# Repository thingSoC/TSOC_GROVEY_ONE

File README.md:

# TSOC_GROVEY_ONE
**TSOC_GROVEY_ONE** is a ATMEGA328 based board, an Embedded Module for thingSoC compatible with the Arduino IDE.

The **TSOC_GROVEY_ONE** allows you to connect [thingSoC](http://thingsoc.github.io/), [Mikrobus](http://www.mikroe.com/mikrobus/), 
and/or [Grove System](http://www.seeedstudio.com/blog/2016/03/09/tutorial-intro-to-grove-connectors-for-arduinoraspberry-pi-projects/) 
Modules all at the same time, using the Arduino Development environment, with the the ATMEGA328P processor.
This gives you maximum flexiblity for sensor and actuator, selection and reuse. 

The thingSoC "Grovey Series" was designed as "Everyday Electronics", a no-frills, low cost, approach to modular embedded product design.
thingSoC boards are similar in size to most break-out-boards (BOBs), but feature a standardized stacking pinout, as well as an I2C metadata store (EEPROM)
to indicate what peripherals are installed.

---------------------------------------

[TSOC_GROVEY_ONE](https://github.com/thingSoC/TSOC_GROVEY_ONE/)

* [thingSoC Compliant Module](http://www.thingsoc.com)
* [Mikrobus Compatible Module](http://www.mikroe.com/mikrobus/) 
* 5V Nominal Power Input
* 5V or 3.3V Operation
* Supports Analog  Inputs  (ADC) 
* Supports Digital Outputs (GPIO)
* Supports Digital Inputs  (GPIO)
* Supports I2C Interface
* Supports UART Interface
* Supports SPI Interface

---------------------------------------
## Example Applications

* [Weather Sensor](http://www.mikroe.com/click/weather/) BOSCH BME280 Temp, Humidity, Air Pressure
* [Methane Sensor](http://www.mikroe.com/click/methane/) MQ-4 Sensor for Methane (CH4) 
* [Air Quality Sensor](http://www.mikroe.com/click/air-quality/) MQ-135 Sensor for Harmful Gasses
* [Lightning Sensor](http://www.mikroe.com/click/thunder/) AS3935 Lighting Strike Detector
* [Controlled Relay](http://www.mikroe.com/click/relay/) G6D1AASI Power Relay Control Module

---------------------------------------
## 3D Model (Sketchup)

---------------------------------------
## Project Status

* 09/02/2016 : Revision 2.0 Release for PCB fab

## Revision 2.0 Notes: ##

* Add FTDI Connector

---------------------------------------

## Documentation Index <a name="documentation_index"/>

[Quick Start Guide](https://github.com/thingSoC/TSOC_GROVEY_ONE/blob/master/TSOC_GROVEY_ONE/docs/QuickStart.md)

[User Guide](https://github.com/thingSoC/TSOC_GROVEY_ONE/blob/master/TSOC_GROVEY_ONE/docs/UserGuide.md)

[Theory of Operation](https://github.com/thingSoC/TSOC_GROVEY_ONE/blob/master/TSOC_GROVEY_ONE/docs/TheoryOfOperation.md)

[thingSoC Organization Website](http://thingSoC.github.io)

[thingSoC FAQ - Frequently Asked Questions](http://thingsoc.github.io/support/faq.html)

---------------------------------------

[  
*thingSoC*](http://thingsoc.github.io)

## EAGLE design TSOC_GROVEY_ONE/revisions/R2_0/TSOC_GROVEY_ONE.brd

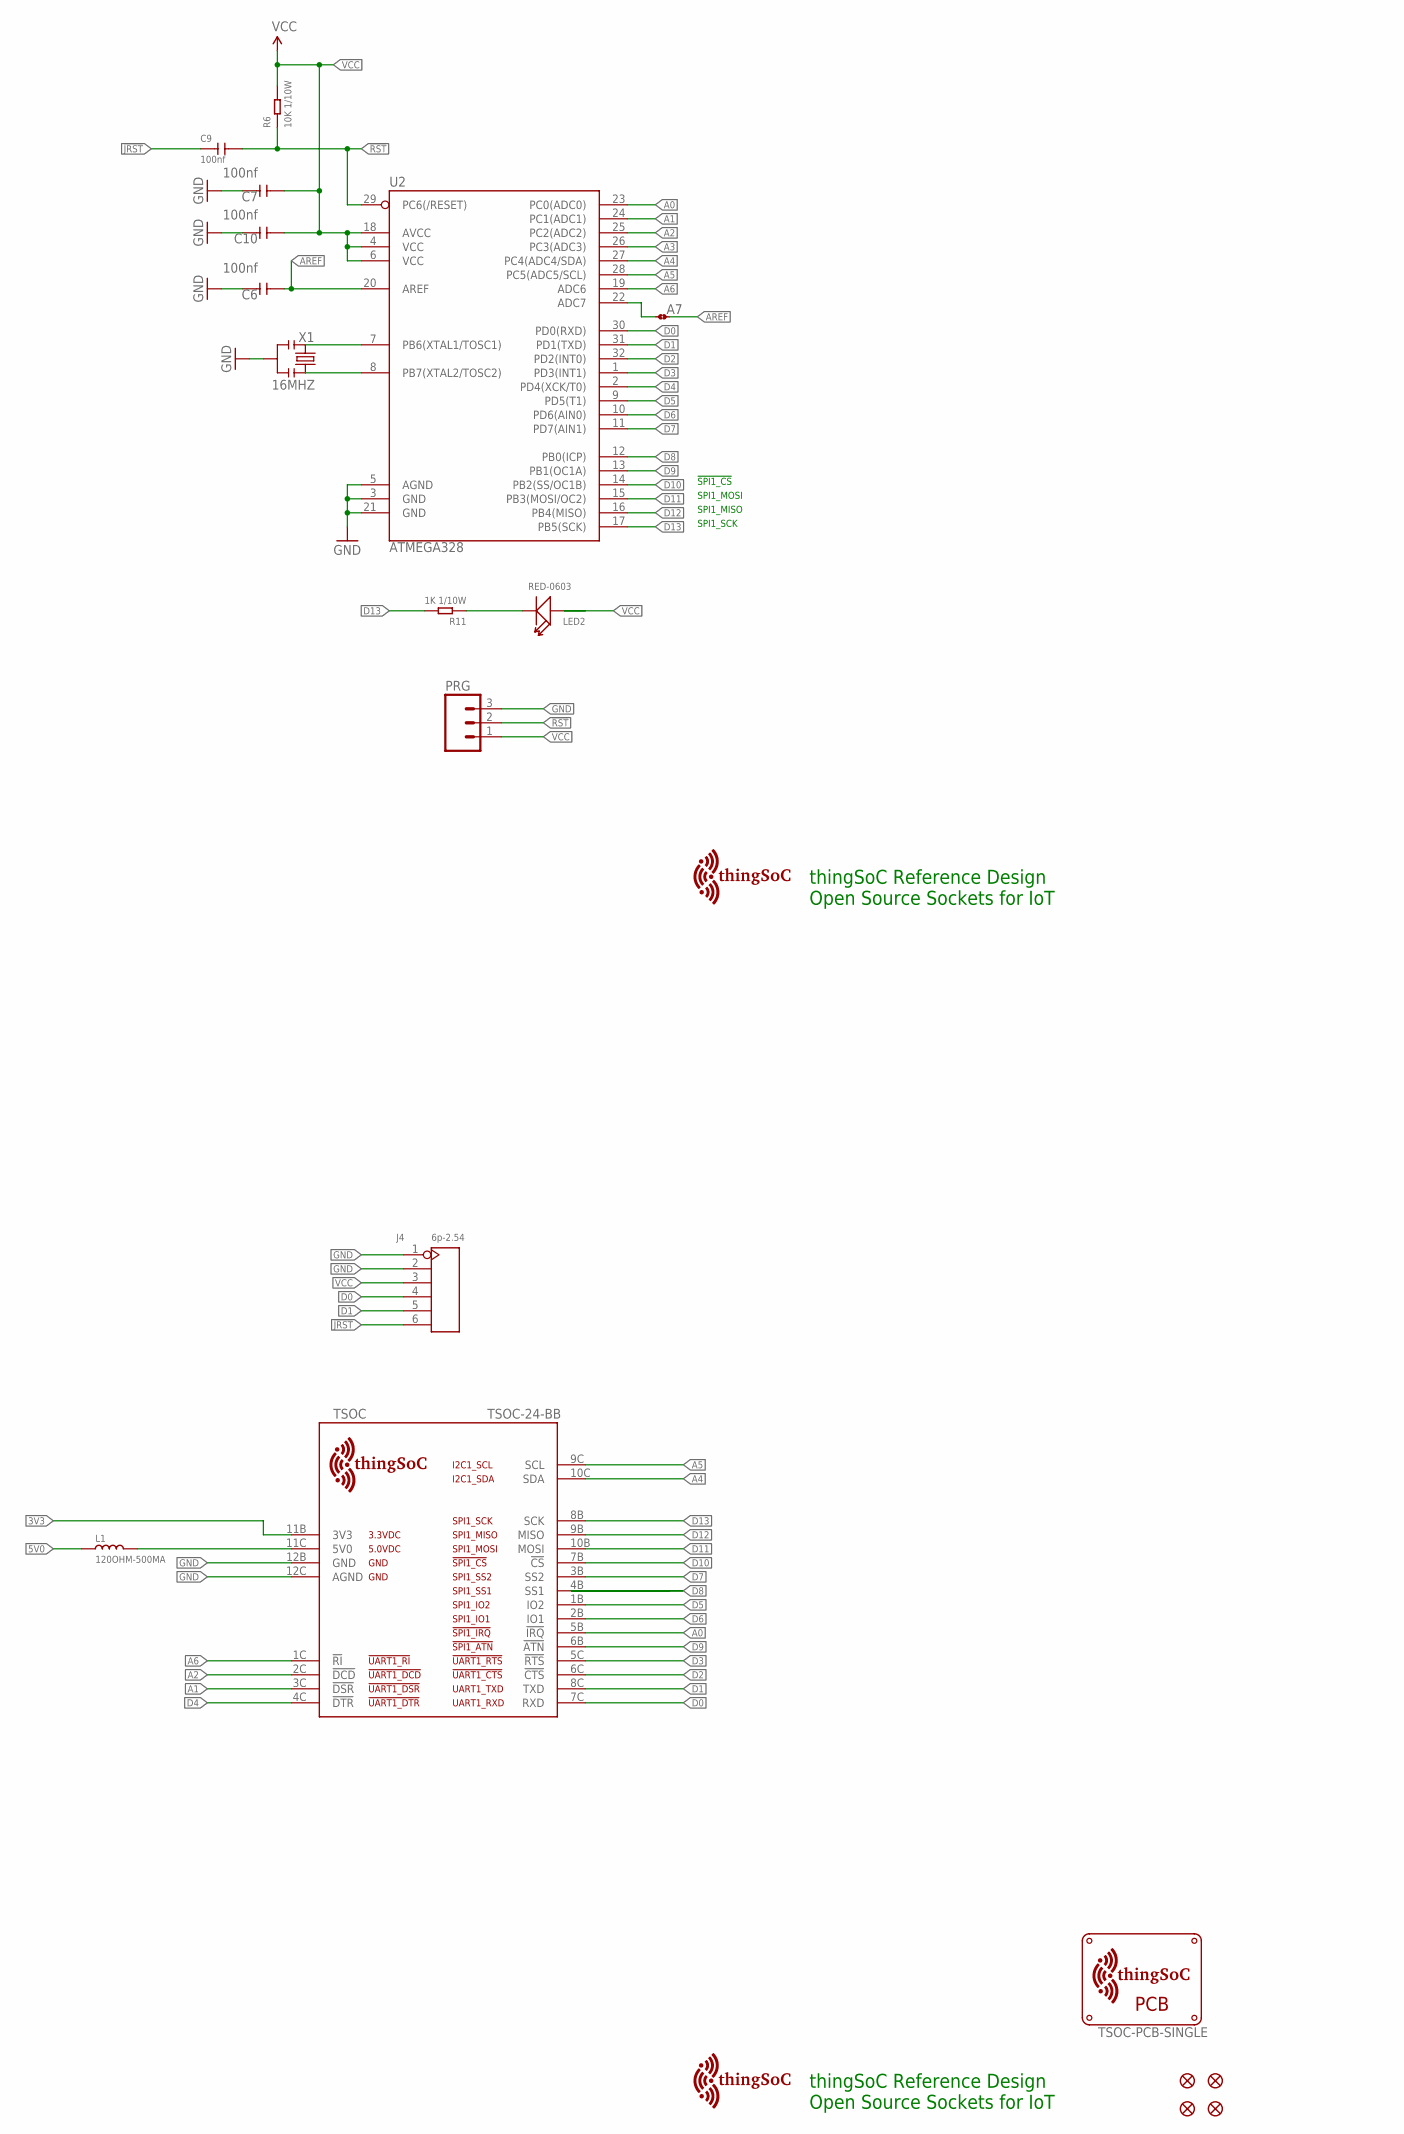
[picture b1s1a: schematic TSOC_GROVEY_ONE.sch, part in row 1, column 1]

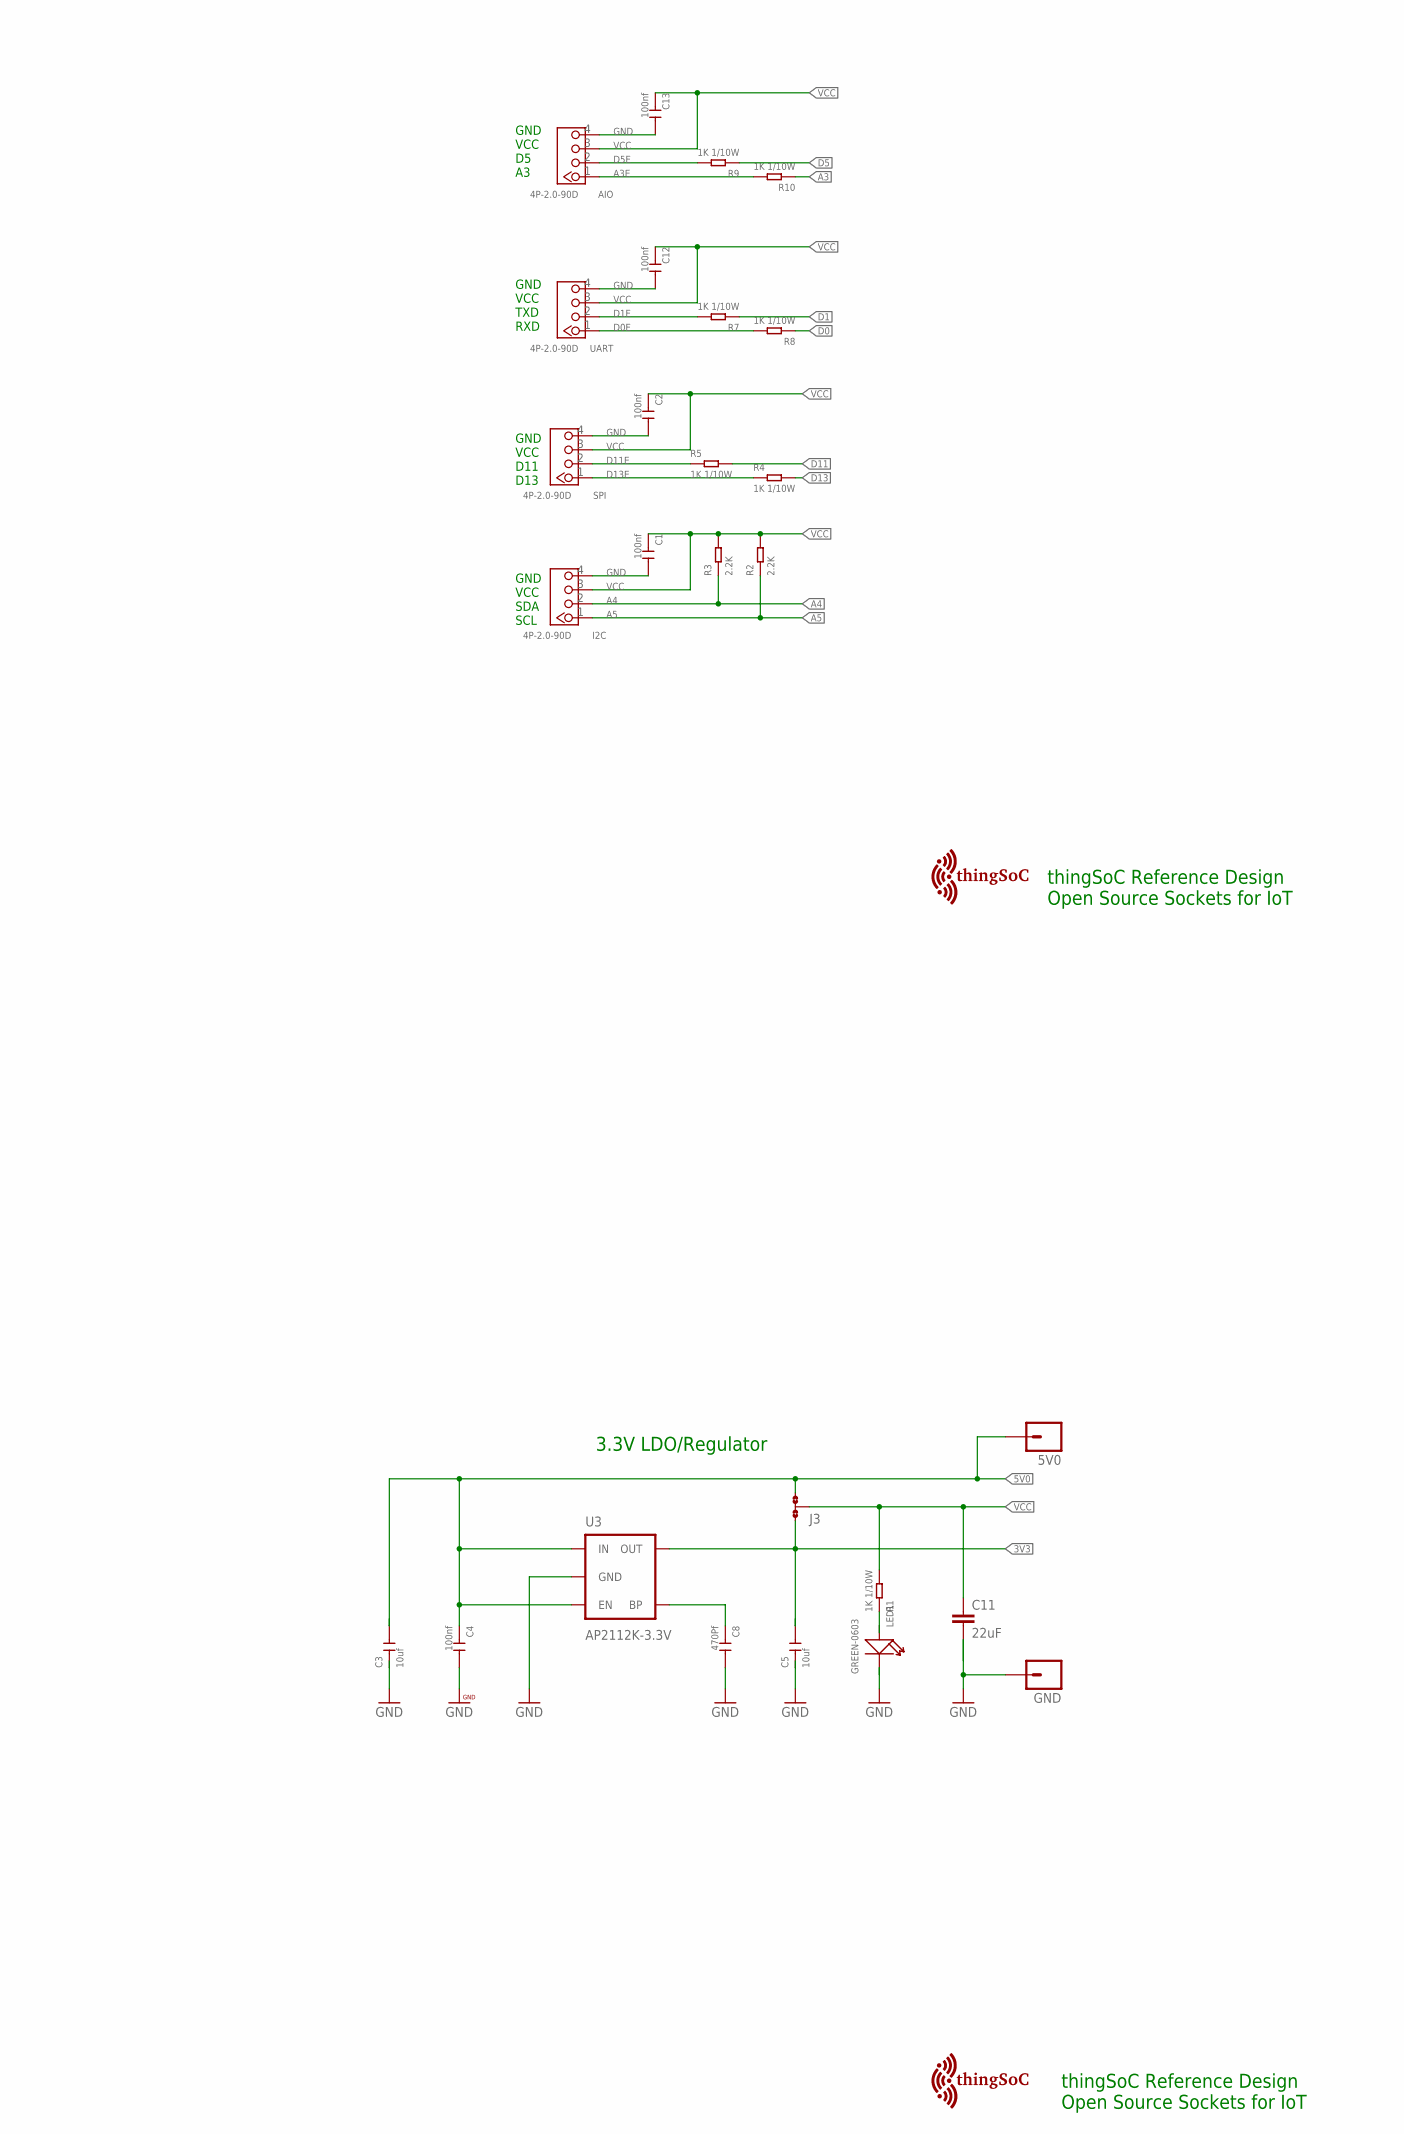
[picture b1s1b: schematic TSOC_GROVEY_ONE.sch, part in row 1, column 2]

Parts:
5V0: M01PTH; 1X01
$$U$1: TSOC-PCB-SINGLE; TSOC-BB-BRD-DIM
A7: JMP-2-NO
AIO: 4P-2.0-90D; HW4-2.0-90D
C1, C2, C4, C6, C7, C9, C10, C12, C13: 100nf; C0603
C3, C5: 10uf; C0603
C8: 470Pf; C0603
C11: 22uF; EIA-1206
FID1, FID2, FID3, FID4: FIDUCIALUFIDUCIAL; MICRO-FIDUCIAL
GND: M01PTH; 1X01
I2C: 4P-2.0-90D; HW4-2.0-90D
J3: NO; JMP-3-NO-PTH-2.54
J4: 6p-2.54; H6-2.54
L1: 120OHM-500MA; L0603
LED1: GREEN-0603; LED-0603
LED2: RED-0603; LED-0603
PRG: M03PTH; 1X03
R1, R4, R5, R7, R8, R9, R10, R11: 1K 1/10W; R0603
R2, R3: 2.2K; R0603
R6: 10K 1/10W; R0603
SPI: 4P-2.0-90D; HW4-2.0-90D
TSOC: TSOC-24-BB; TSOC-BB-S24
U2: ATMEGA328; TQFP32-08
U3: AP2112K-3.3V; SOT23-5
U$1, U$101, U$103: TSOC-LOGO-SMALL; TSOC-LOGO-SML
U$102: TSOC-LOGO-LRG
UART: 4P-2.0-90D; HW4-2.0-90D
X1: 16MHZ; X3-SMD-3.6X1.3X0.8MM

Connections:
3V3: C5.2, J3.1, TSOC.11B (3V3), U3.5 (OUT)
5V0: 5V0.1, C3.2, C4.1, J3.3, L1.1, U3.1 (IN), U3.3 (EN)
!JRST: C9.1, J4.6
!RST: C9.2, PRG.2, R6.1, U2.29 (PC6(/RESET))
A0: TSOC.5B (!IRQ), U2.23 (PC0(ADC0))
A1: TSOC.3C (!DSR), U2.24 (PC1(ADC1))
A2: TSOC.2C (!DCD), U2.25 (PC2(ADC2))
A3: R10.1, U2.26 (PC3(ADC3))
A3E: AIO.1, R10.2
A4: I2C.2, R3.1, TSOC.10C (SDA), U2.27 (PC4(ADC4/SDA))
A5: I2C.1, R2.1, TSOC.9C (SCL), U2.28 (PC5(ADC5/SCL))
A6: TSOC.1C (!RI), U2.19 (ADC6)
A7: A7.1, U2.22 (ADC7)
AREF: A7.2, C6.2, U2.20 (AREF)
BYPASS1: C8.1, U3.4 (BP)
D0: J4.4, R8.1, TSOC.7C (RXD), U2.30 (PD0(RXD))
D0E: R8.2, UART.1
D1: J4.5, R7.1, TSOC.8C (TXD), U2.31 (PD1(TXD))
D1E: R7.2, UART.2
D2: TSOC.6C (!CTS), U2.32 (PD2(INT0))
D3: TSOC.5C (!RTS), U2.1 (PD3(INT1))
D4: TSOC.4C (!DTR), U2.2 (PD4(XCK/T0))
D5: R9.1, TSOC.1B (IO2), U2.9 (PD5(T1))
D5E: AIO.2, R9.2
D6: TSOC.2B (IO1), U2.10 (PD6(AIN0))
D7: TSOC.3B (SS2), U2.11 (PD7(AIN1))
D8: TSOC.4B (SS1), U2.12 (PB0(ICP))
D9: TSOC.6B (!ATN), U2.13 (PB1(OC1A))
D10: TSOC.7B (!CS), U2.14 (PB2(SS/OC1B))
D11: R5.2, TSOC.10B (MOSI), U2.15 (PB3(MOSI/OC2))
D11E: R5.1, SPI.2
D12: TSOC.9B (MISO), U2.16 (PB4(MISO))
D13: R4.2, R11.2, TSOC.8B (SCK), U2.17 (PB5(SCK))
D13E: R4.1, SPI.1
GND: AIO.4, C1.2, C2.2, C3.1, C4.2, C5.1, C6.1, C7.1, C8.2, C10.1, C11.2, C12.2, C13.2, GND.1, I2C.4, J4.1, J4.2, LED1.-, PRG.3, SPI.4, TSOC.12B (GND), TSOC.12C (AGND), U2.3 (GND), U2.5 (AGND), U2.21 (GND), U3.2 (GND), UART.4, X1.2
LEDR: LED2.-, R11.1
unnamed: LED1.+, R1.1
TSOC_5V0: L1.2, TSOC.11C (5V0)
VCC: AIO.3, C1.1, C2.1, C7.2, C10.2, C11.1, C12.1, C13.1, I2C.3, J3.2, J4.3, LED2.+, PRG.1, R1.2, R2.2, R3.2, R6.2, SPI.3, U2.4 (VCC), U2.6 (VCC), U2.18 (AVCC), UART.3
XIN: U2.7 (PB6(XTAL1/TOSC1)), X1.3
XOUT: U2.8 (PB7(XTAL2/TOSC2)), X1.1

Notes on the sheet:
thingSoC Reference Design Open Source Sockets for IoT
SPI1_SCK
SPI1_MISO
SPI1_MOSI
!SPI1_CS
3.3V LDO/Regulator
SDA
SCL
VCC
GND
RXD
TXD
D11
D13

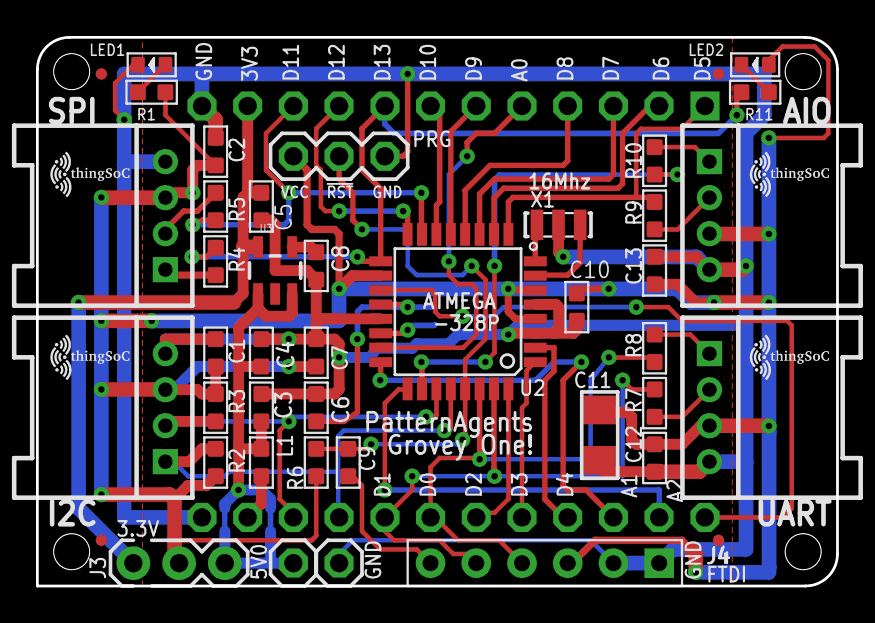
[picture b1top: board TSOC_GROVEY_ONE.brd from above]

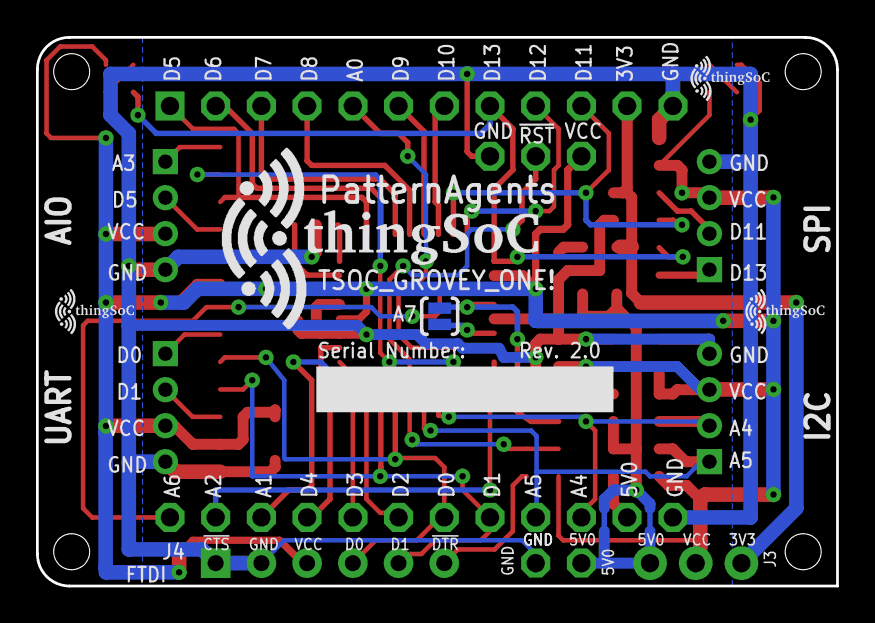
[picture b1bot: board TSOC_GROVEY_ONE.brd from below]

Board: 2 copper layers, 44.5 x 30.5 mm, 54 parts (5 on the bottom side), 41 nets.

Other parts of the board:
$$U$2, $$U$3: TSOC-LOGO-SMALL; TSOC-LOGO-SML
U$3, U$100: TSOC-LOGO-SMALL; TSOC-LOGO-SML

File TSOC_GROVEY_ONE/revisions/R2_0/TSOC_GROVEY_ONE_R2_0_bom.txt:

Partlist exported from U:/PatternAgents/eagle/TSOC_Modules/TSOC_GROVEY_ONE/TSOC_GROVEY_ONE/revisions/R2_0/TSOC_GROVEY_ONE_R2_0_gerbers/TSOC_GROVEY_ONE.sch at 12/29/2016 11:41:01 AM

Qty Value             Device                                          Package              Parts                                 Description                           
1                     JMP-2-NO                                        JMP-2-NO             A7                                    Two Terminal Jumper - Normally Open   
2                     M01PTH                                          1X01                 5V0, GND                              Header 1                              
1                     M03PTH                                          1X03                 PRG                                   Header 3                              
9   100nf             CERAMIC-100NF-50V-10%-X7R(0603)                 C0603                C1, C2, C4, C6, C7, C9, C10, C12, C13 302010138                             
1   10K 1/10W         SMD-RES-10K-5%-1/10W(0603)                      R0603                R6                                    301010293                             
2   10uf              CERAMIC-10UF-10V-10%-X5R(0603)                  C0603                C3, C5                                302010103                             
1   120OHM-500MA      SMD-FERRITE-CHIP-120-OHM-500MA(0603)            L0603                L1                                    303030001                             
1   16MHZ             SMD-RESONATOR-16MHZ-15PF-0.5%-40R(3P-3.2X1.3MM) X3-SMD-3.6X1.3X0.8MM X1                                    306030002                             
8   1K 1/10W          SMD-RES-1K-5%-1/10W(0603)                       R0603                R1, R4, R5, R7, R8, R9, R10, R11      301010291                             
2   2.2K              SMD-RES-2.2K-5%-1/10W(0603)                     R0603                R2, R3                                301010124                             
1   22uF              CAP-1206                                        EIA-1206             C11                                   Ceramic Capacitor SMD                 
1   470Pf             CERAMIC-100NF-50V-10%-X7R(0603)                 C0603                C8                                    302010138                             
4   4P-2.0-90D        GROVE-CONNECTOR-DIP-90D(4P-2.0)                 HW4-2.0-90D          AIO, I2C, SPI, UART                   320110034                             
1   6p-2.54           DIP-BLACK-MALE-HEADER(6P-2.54)                  H6-2.54              J4                                    320020078                             
1   AP2112K-3.3V      V_REG_LDOSMD                                    SOT23-5              U1                                    Voltage Regulator LDO                 
1   ATMEGA328         ATMEGA168                                       TQFP32-08            U2                                                                          
4   FIDUCIALUFIDUCIAL FIDUCIALUFIDUCIAL                               MICRO-FIDUCIAL       FID1, FID2, FID3, FID4                Fiducial Alignment Points             
1   GREEN-0603        SMD-LED-CLEAR-GREEN(0603)                       LED-0603             LED1                                  304090043                             
1   NO                JMP-3-NO-PTH                                    JMP-3-NO-PTH-2.54    J3                                    Three Terminal Jumper - Normally Open 
1   RED-0603          SMD-LED-CLEAR-GREEN(0603)                       LED-0603             LED2                                  304090043                             
1   TSOC-24-BB        TSOC-24-BB                                      TSOC-BB-S24          TSOC                                  thingSoC Twenty-Four(24) Pin Socket   
1   TSOC-LOGO-LRG     TSOC-LOGO-LRG                                   TSOC-LOGO-LRG        U$102                                 thingSoC Logo                         
3   TSOC-LOGO-SMALL   TSOC-LOGO-SMALL                                 TSOC-LOGO-SML        U$1, U$101, U$103                     thingSoC Logo                         
1   TSOC-PCB-SINGLE   TSOC-PCB-SINGLE                                 TSOC-BB-BRD-DIM      $$U$1                                 thingSoC PCB Outlines

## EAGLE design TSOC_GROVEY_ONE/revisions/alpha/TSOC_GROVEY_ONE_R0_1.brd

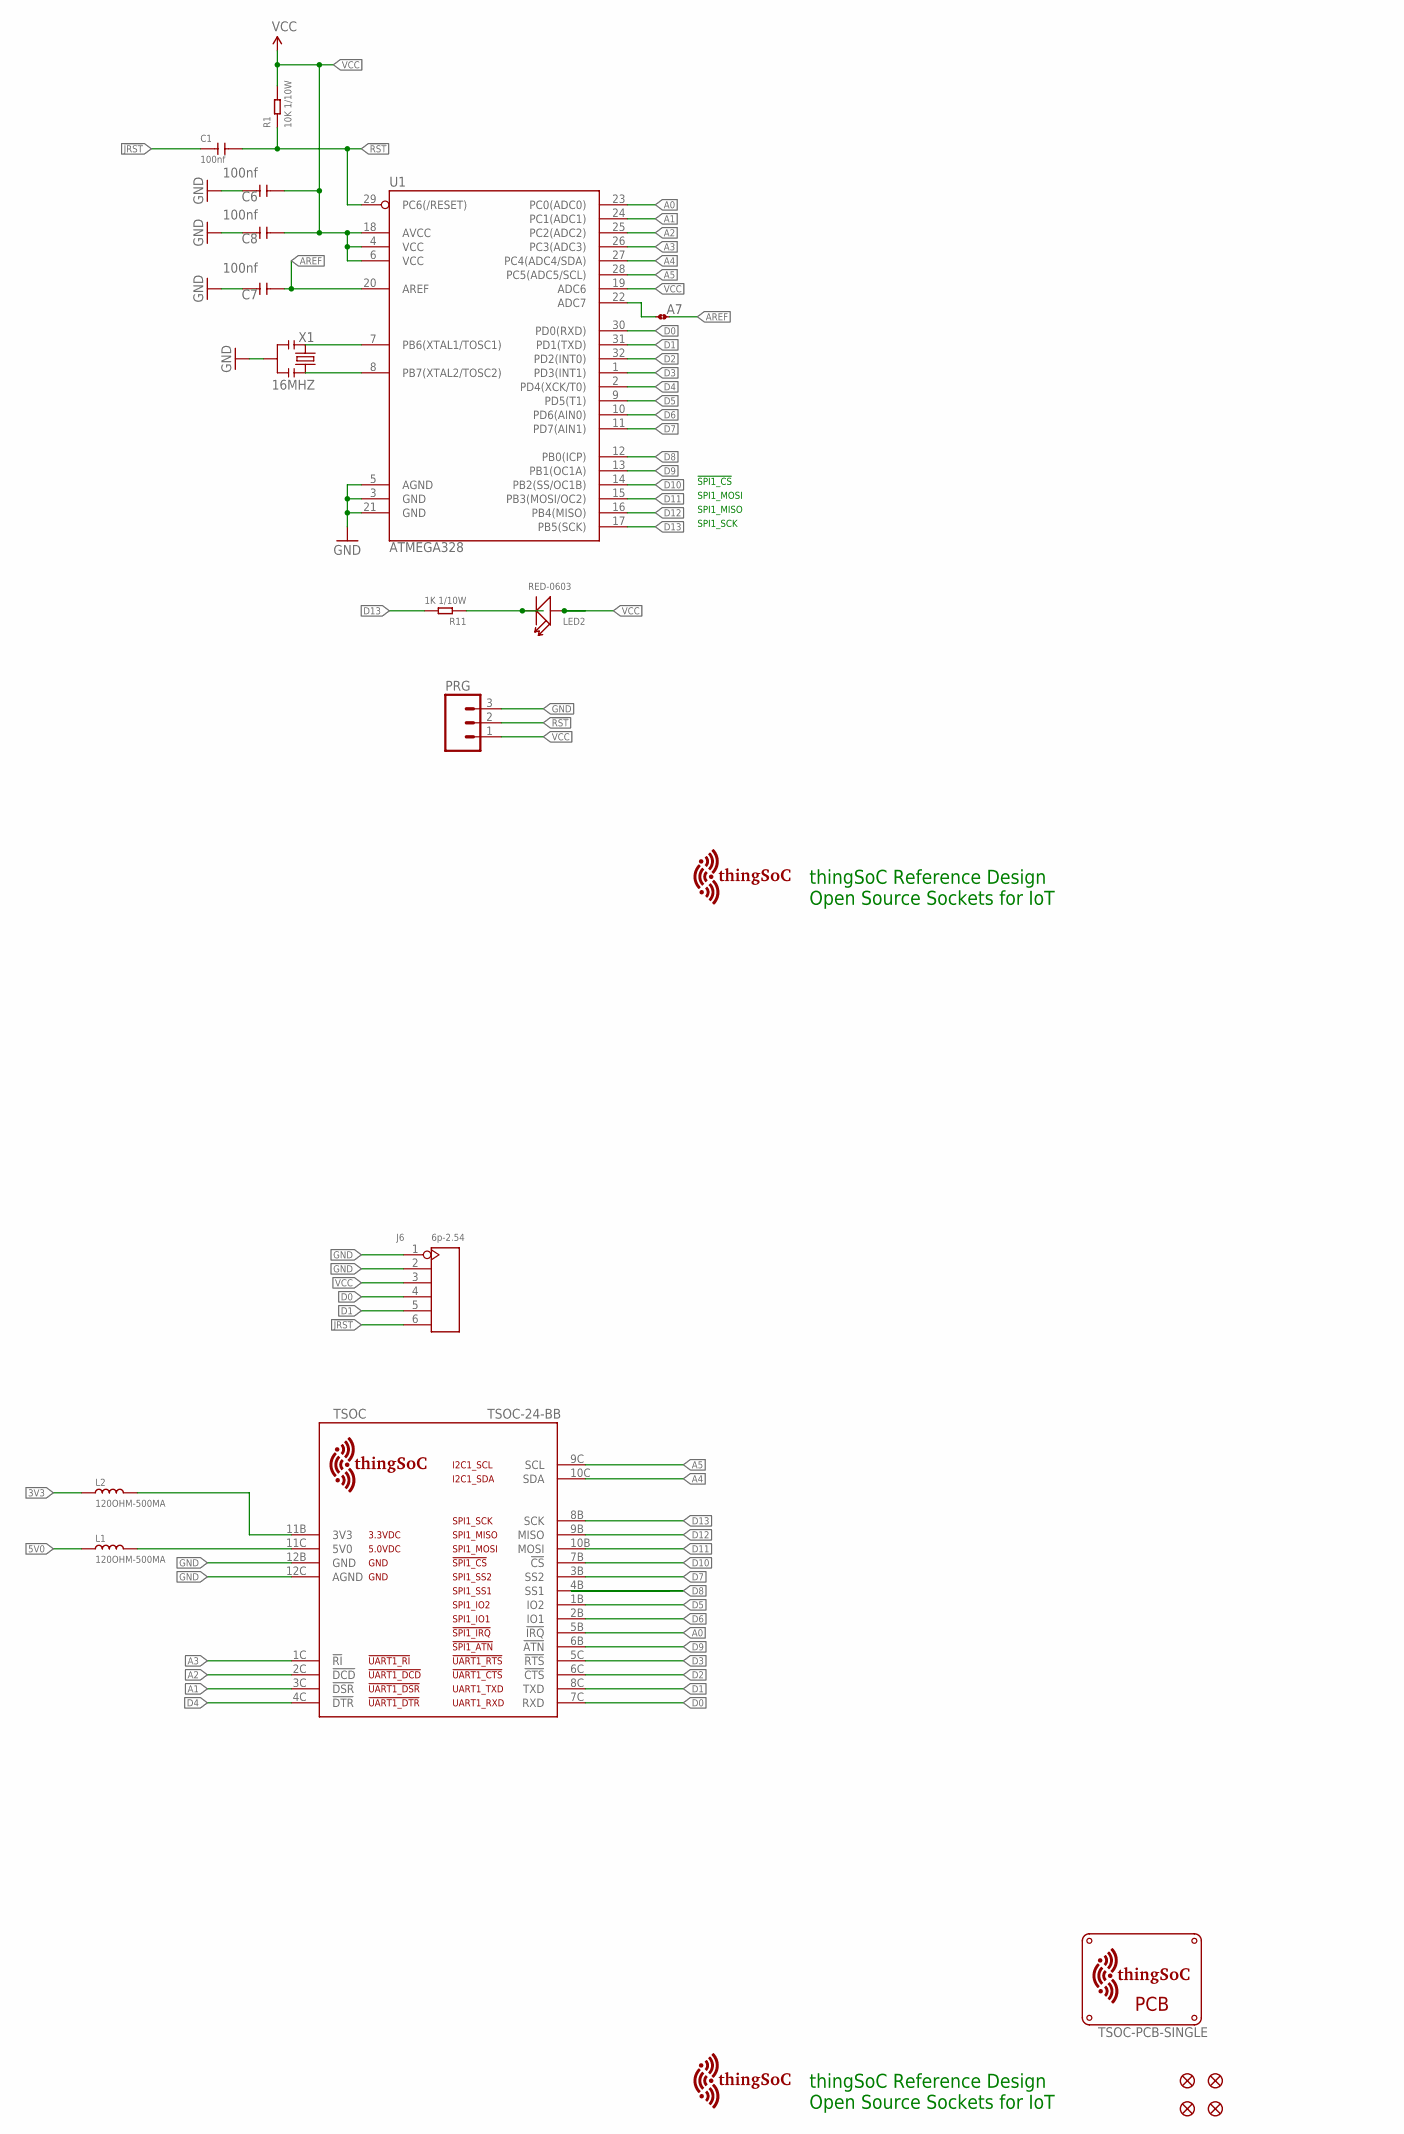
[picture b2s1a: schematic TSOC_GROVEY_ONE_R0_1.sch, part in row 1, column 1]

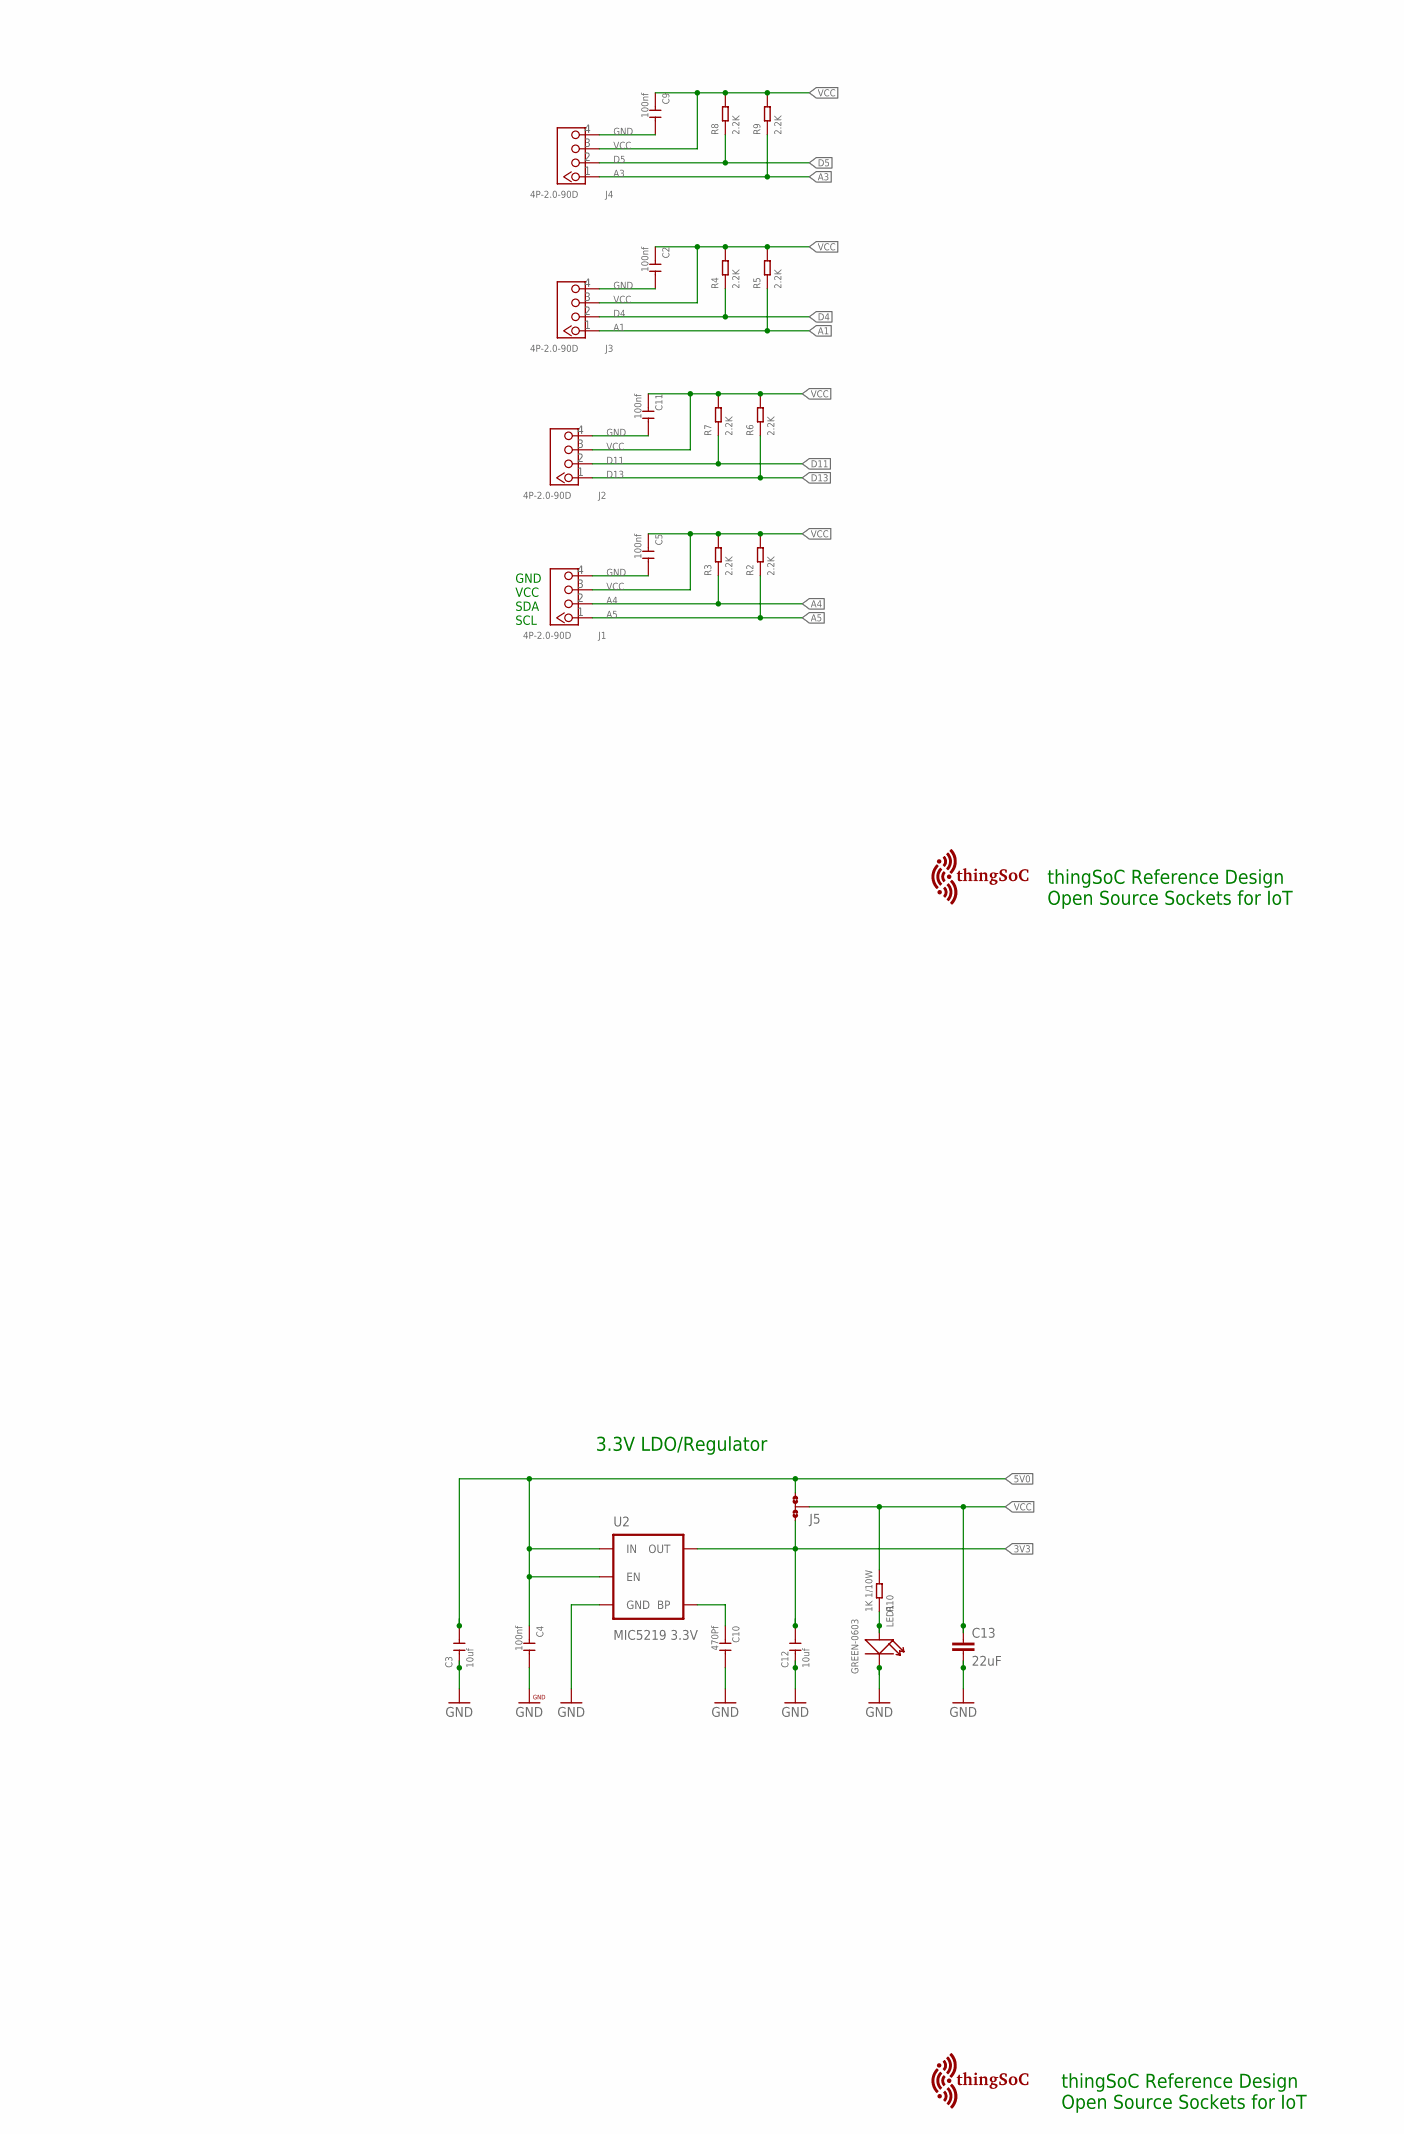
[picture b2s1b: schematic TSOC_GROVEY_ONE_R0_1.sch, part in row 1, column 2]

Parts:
$$U$2: TSOC-PCB-SINGLE; TSOC-BB-BRD-DIM
A7: JMP-2-NO
C1, C2, C4, C5, C6, C7, C8, C9, C11: 100nf; C0603
C3, C12: 10uf; C0603
C10: 470Pf; C0603
C13: 22uF; EIA-1206
FID1, FID2, FID3, FID4: FIDUCIALUFIDUCIAL; MICRO-FIDUCIAL
J1, J2, J3, J4: 4P-2.0-90D; HW4-2.0-90D
J5: NO; JMP-3-NO-PTH-2.54
J6: 6p-2.54; H6-2.54
L1, L2: 120OHM-500MA; L0603
LED1: GREEN-0603; LED-0603
LED2: RED-0603; LED-0603
PRG: M03PTH; 1X03
R1: 10K 1/10W; R0603
R2, R3, R4, R5, R6, R7, R8, R9: 2.2K; R0603
R10, R11: 1K 1/10W; R0603
TSOC: TSOC-24-BB; TSOC-BB-S24
U1: ATMEGA328; TQFP32-08
U2: MIC5219 3.3V; SOT23-5
U$3, U$100, U$103: TSOC-LOGO-SMALL; TSOC-LOGO-SML
U$101: TSOC-LOGO-LRG
X1: 16MHZ; X3-SMD-3.6X1.3X0.8MM

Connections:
3V3: C12.2, J5.1, L2.1, U2.5 (OUT)
5V0: C3.2, C4.1, J5.3, L1.1, U2.1 (IN), U2.3 (EN)
!JRST: C1.1, J6.6
!RST: C1.2, PRG.2, R1.1, U1.29 (PC6(/RESET))
A0: TSOC.5B (!IRQ), U1.23 (PC0(ADC0))
A1: J3.1, R5.1, TSOC.3C (!DSR), U1.24 (PC1(ADC1))
A2: TSOC.2C (!DCD), U1.25 (PC2(ADC2))
A3: J4.1, R9.1, TSOC.1C (!RI), U1.26 (PC3(ADC3))
A4: J1.2, R3.1, TSOC.10C (SDA), U1.27 (PC4(ADC4/SDA))
A5: J1.1, R2.1, TSOC.9C (SCL), U1.28 (PC5(ADC5/SCL))
A7: A7.1, U1.22 (ADC7)
AREF: A7.2, C7.2, U1.20 (AREF)
BYPASS1: C10.1, U2.4 (BP)
D0: J6.4, TSOC.7C (RXD), U1.30 (PD0(RXD))
D1: J6.5, TSOC.8C (TXD), U1.31 (PD1(TXD))
D2: TSOC.6C (!CTS), U1.32 (PD2(INT0))
D3: TSOC.5C (!RTS), U1.1 (PD3(INT1))
D4: J3.2, R4.1, TSOC.4C (!DTR), U1.2 (PD4(XCK/T0))
D5: J4.2, R8.1, TSOC.1B (IO2), U1.9 (PD5(T1))
D6: TSOC.2B (IO1), U1.10 (PD6(AIN0))
D7: TSOC.3B (SS2), U1.11 (PD7(AIN1))
D8: TSOC.4B (SS1), U1.12 (PB0(ICP))
D9: TSOC.6B (!ATN), U1.13 (PB1(OC1A))
D10: TSOC.7B (!CS), U1.14 (PB2(SS/OC1B))
D11: J2.2, R7.1, TSOC.10B (MOSI), U1.15 (PB3(MOSI/OC2))
D12: TSOC.9B (MISO), U1.16 (PB4(MISO))
D13: J2.1, R6.1, R11.2, TSOC.8B (SCK), U1.17 (PB5(SCK))
GND: C2.2, C3.1, C4.2, C5.2, C6.1, C7.1, C8.1, C9.2, C10.2, C11.2, C12.1, C13.2, J1.4, J2.4, J3.4, J4.4, J6.1, J6.2, LED1.-, PRG.3, TSOC.12B (GND), TSOC.12C (AGND), U1.3 (GND), U1.5 (AGND), U1.21 (GND), U2.2 (GND), X1.2
LEDR: LED2.-, R11.1
unnamed: LED1.+, R10.1
TSOC_3V3: L2.2, TSOC.11B (3V3)
TSOC_5V0: L1.2, TSOC.11C (5V0)
VCC: C2.1, C5.1, C6.2, C8.2, C9.1, C11.1, C13.1, J1.3, J2.3, J3.3, J4.3, J5.2, J6.3, LED2.+, PRG.1, R1.2, R2.2, R3.2, R4.2, R5.2, R6.2, R7.2, R8.2, R9.2, R10.2, U1.4 (VCC), U1.6 (VCC), U1.18 (AVCC), U1.19 (ADC6)
XIN: U1.7 (PB6(XTAL1/TOSC1)), X1.3
XOUT: U1.8 (PB7(XTAL2/TOSC2)), X1.1

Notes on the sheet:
thingSoC Reference Design Open Source Sockets for IoT
SPI1_SCK
SPI1_MISO
SPI1_MOSI
!SPI1_CS
3.3V LDO/Regulator
SDA
SCL
VCC
GND

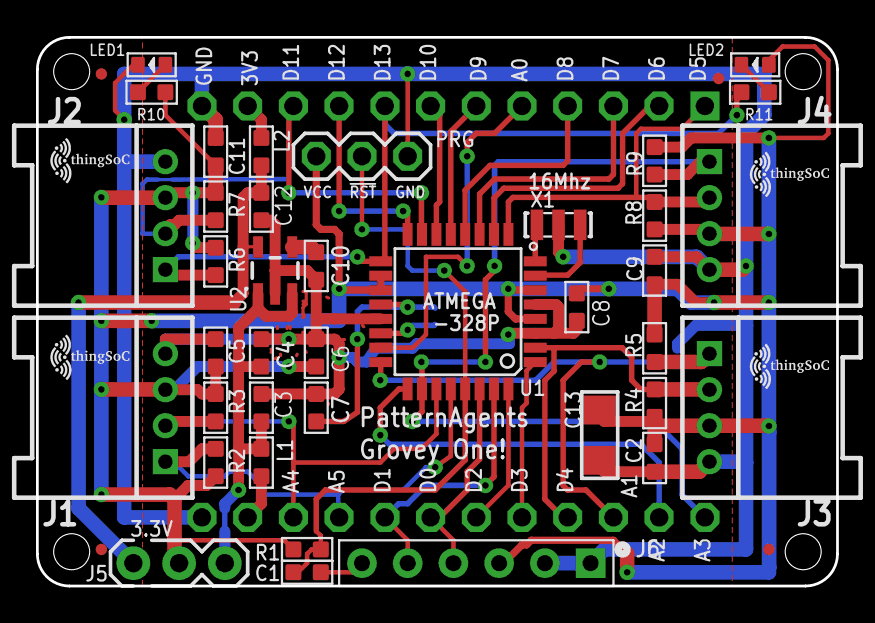
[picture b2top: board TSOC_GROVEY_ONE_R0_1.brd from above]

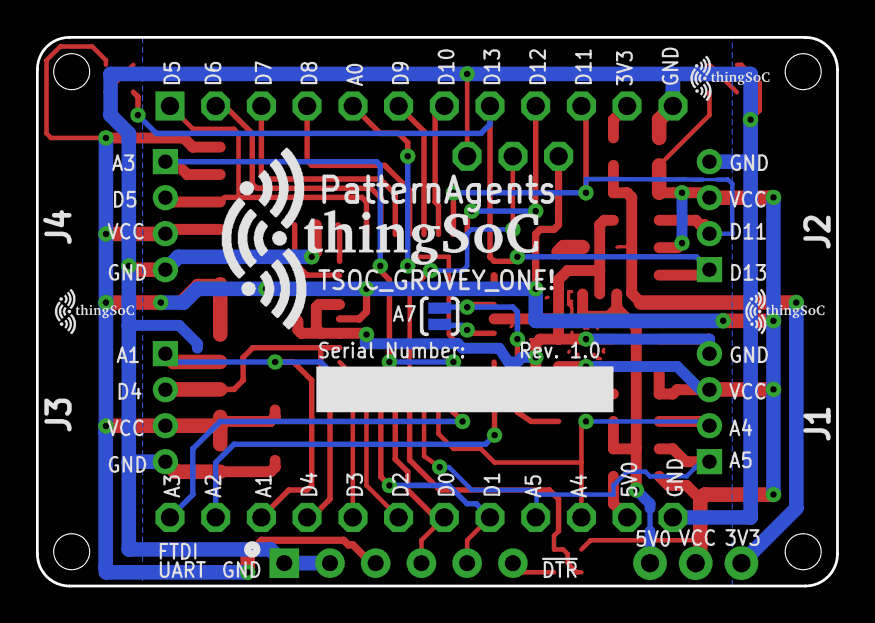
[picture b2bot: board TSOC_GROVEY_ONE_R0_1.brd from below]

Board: 2 copper layers, 44.5 x 30.5 mm, 53 parts (5 on the bottom side), 35 nets.

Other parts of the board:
U$1, U$4, U$5, U$102: TSOC-LOGO-SMALL; TSOC-LOGO-SML

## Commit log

2016-09-02 initial version
2016-09-04 update docs
2017-01-16 update documetation

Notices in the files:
parts and their libraries:
PatternAgents-Beautify: License : http://creativecommons.org/licenses/by-sa/3.0
(Creative Commons 3.0)
thingSoC: License : http://creativecommons.org/licenses/by-sa/4.0
(Creative Commons 4.0)
